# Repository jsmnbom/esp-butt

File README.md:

# esp-butt

Bluetooth intimate hardware (sex toys, etc) controller powered by [buttplug.io](https://buttplug.io/).

## Status

This project is still in fairly early development, it has some quirks and rough edges but is generally functional. Feel free to contact me if you are interested in building your own or contributing to the project.

## Documentation

<div align="center">
  <table>
    <tr>
      <td><h3 align="center"><a href="https://jsmnbom.github.io/esp-butt/">🏠<br/>Home</a></h3></td>
      <td><h3 align="center"><a href="https://jsmnbom.github.io/esp-butt/hardware">🛠️<br/>Hardware</a></h3></td>
      <td><h3 align="center"><a href="https://jsmnbom.github.io/esp-butt/hardware">📋<br/>BOM</a></h3></td>
      <td><h3 align="center"><a href="https://jsmnbom.github.io/esp-butt/hardware">📐<br/>Schematic</a></h3></td>
      <td><h3 align="center"><a href="https://jsmnbom.github.io/esp-butt/hardware">🟩<br/>PCB</a></h3></td>
      <td><h3 align="center"><a href="https://jsmnbom.github.io/esp-butt/hardware">🧊<br/>3D Models</a></h3></td>
      <td><h3 align="center"><a href="https://jsmnbom.github.io/esp-butt/firmware">⚙️<br/>Firmware</a></h3></td>
    </tr>
  </table>
</div>

## Contributing

I welcome contributions with open arms. If you have ideas, suggestions for improvements, or want to help out with development, please don't hesitate to reach out or submit a pull request.

## License

This project uses multiple licenses depending on the component:

| Component | License |
|-----------|---------|
| `src/` — firmware source code | [MIT](https://opensource.org/licenses/MIT) |
| `docs/` — documentation | [MIT](https://opensource.org/licenses/MIT) |
| `cad/` — CAD files | [MIT](https://opensource.org/licenses/MIT) |
| `img/` — images | [CC BY-SA 4.0](https://creativecommons.org/licenses/by-sa/4.0/) |
| `pcb/` — PCB design | [CC BY-SA 4.0](https://creativecommons.org/licenses/by-sa/4.0/) |
| `pcb/kicad-config/10.0/colors/witchhazel.json` | [Apache-2.0](https://www.apache.org/licenses/LICENSE-2.0) — © [Thea Flowers](https://github.com/theacodes/witchhazel) |
| `pcb/esp-butt/3D/` — 3D models | Mixed — see [ATTRIBUTION.md](pcb/esp-butt/3D/ATTRIBUTION.md) |

## Thanks

Thanks to @qdot and the rest of the Buttplug.io contributors doing all the hard work of reverse engineering and protocol design, and also for being generally awesome.

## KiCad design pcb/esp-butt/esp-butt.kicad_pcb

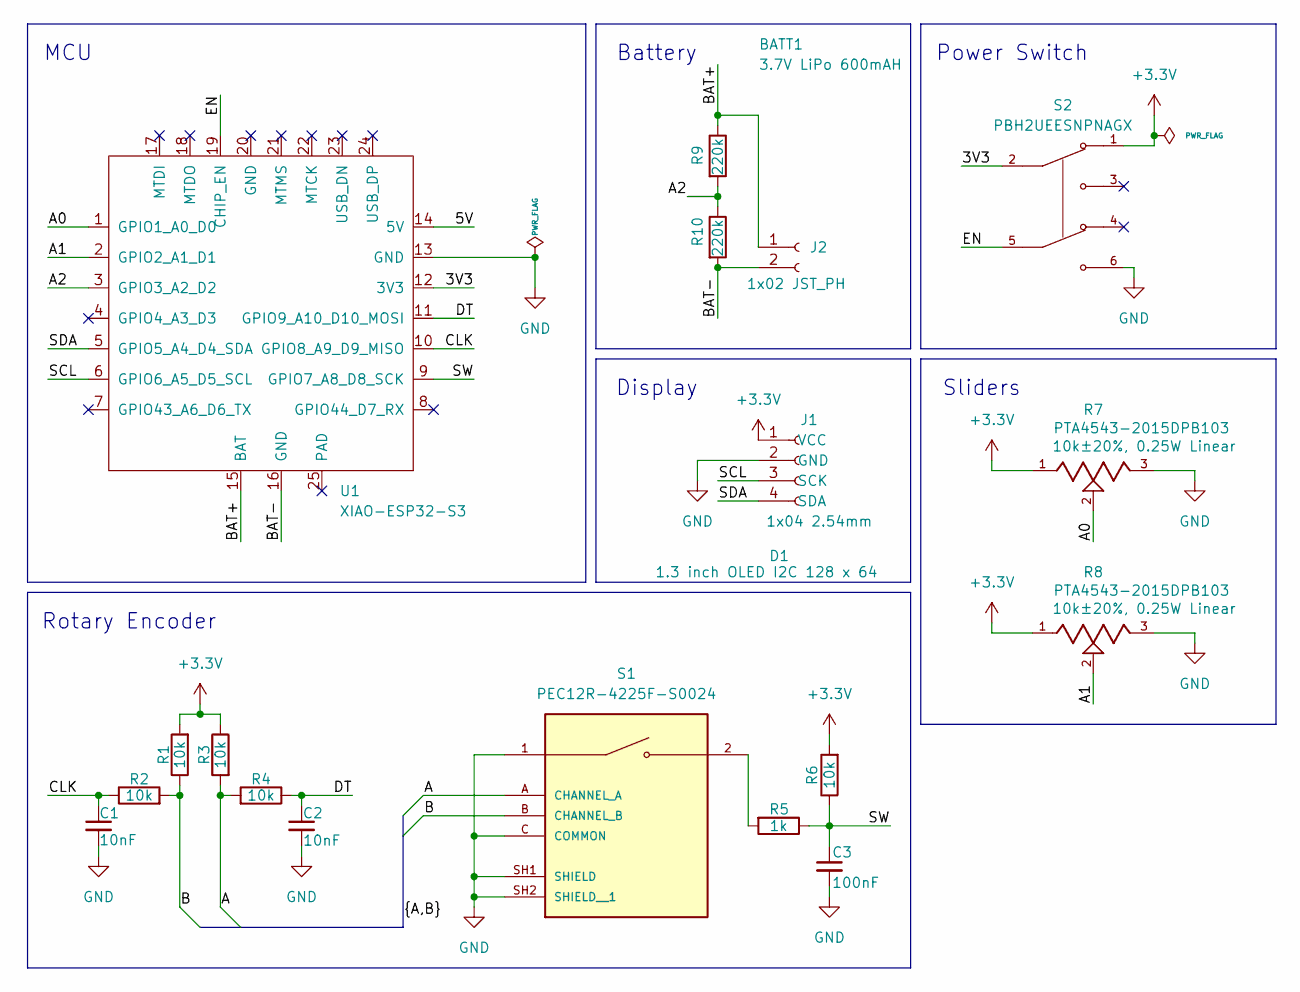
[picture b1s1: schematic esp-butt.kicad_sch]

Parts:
BATT1: 3.7V LiPo 600mAH
C1, C2: 10nF; C_Disc_D5.0mm_W2.5mm_P2.50mm
C3: 100nF; C_Disc_D5.0mm_W2.5mm_P2.50mm
D1: 1.3 inch OLED I2C 128 x 64
J1: 1x04 2.54mm; OLED_128x64_1.3in_I2C_Socket_Vertical
J2: 1x02 JST_PH; JST_PH_B2B-PH-K_1x02_P2.00mm_Vertical
R1, R2, R3, R4, R6: 10k; R_Axial_DIN0207_L6.3mm_D2.5mm_P10.16mm_Horizontal
R5: 1k; R_Axial_DIN0207_L6.3mm_D2.5mm_P10.16mm_Horizontal
R7, R8: PTA4543-2015DPB103; TRIM_PTA4543-2015DPB103; PARTREV 04/21
R9, R10: 220k; R_Axial_DIN0207_L6.3mm_D2.5mm_P10.16mm_Horizontal
S1: PEC12R-4225F-S0024; XDCR_PEC12R-4225F-S0024; PARTREV 07/21
S2: PBH2UEESNPNAGX; SW_PBH2UEESNPNAGX; PARTREV E
U1: XIAO-ESP32-S3; XIAO-ESP32-S3-DIP+

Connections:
+3.3V: J1.1 (VCC), R1.2, R3.1, R6.2, R7.1, R8.1, S2.1
/3V3: S2.2, U1.12 (3V3)
/5V: U1.14 (5V)
/A: R3.2, R4.2, S1.A (CHANNEL_A)
/A0: R7.2, U1.1 (GPIO1_A0_D0)
/A1: R8.2, U1.2 (GPIO2_A1_D1)
/A2: R9.2, R10.1, U1.3 (GPIO3_A2_D2)
/B: R1.1, R2.2, S1.B (CHANNEL_B)
/BAT+: J2.1, R9.1, U1.15 (BAT)
/BAT-: J2.2, R10.2, U1.16 (GND)
/CLK: C1.1, R2.1, U1.10 (GPIO8_A9_D9_MISO)
/DT: C2.1, R4.1, U1.11 (GPIO9_A10_D10_MOSI)
/EN: S2.5, U1.19 (CHIP_EN)
/SCL: J1.3 (SCK), U1.6 (GPIO6_A5_D5_SCL)
/SDA: J1.4 (SDA), U1.5 (GPIO5_A4_D4_SDA)
/SW: C3.1, R5.1, R6.1, U1.9 (GPIO7_A8_D8_SCK)
GND: C1.2, C2.2, C3.2, J1.2 (GND), R7.3, R8.3, S1.1, S1.C (COMMON), S1.SH1 (SHIELD), S1.SH2 (SHIELD__1), S2.6, U1.13 (GND)
unnamed: R5.2, S1.2

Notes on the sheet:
Display
Power Switch
Rotary Encoder
Sliders
MCU
Battery

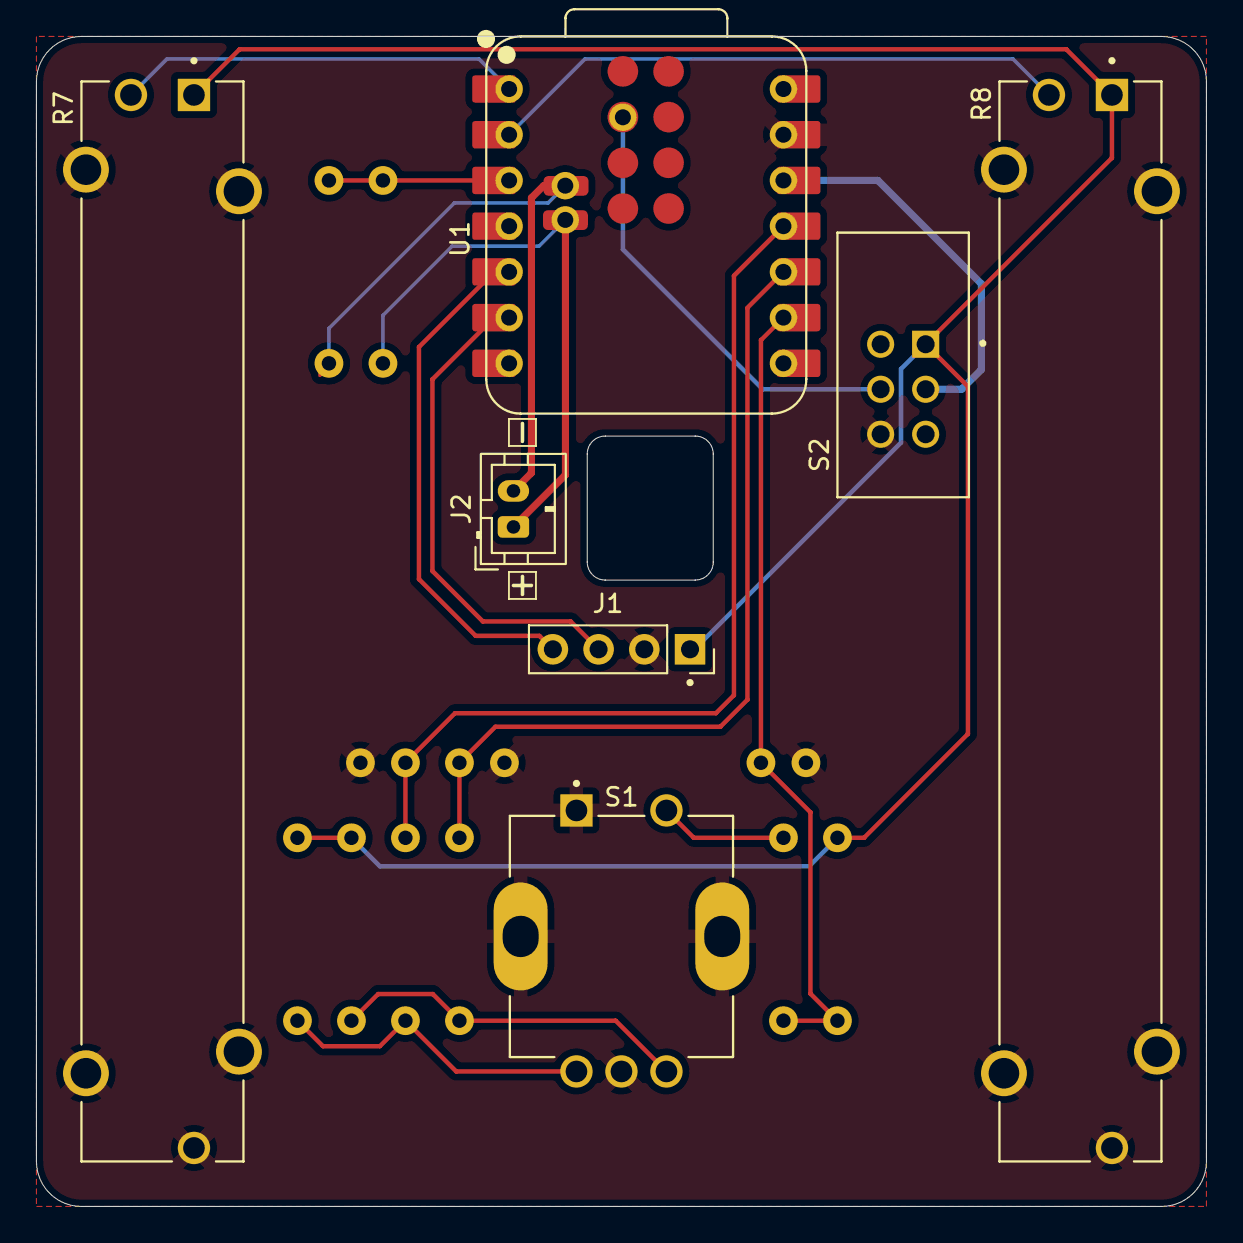
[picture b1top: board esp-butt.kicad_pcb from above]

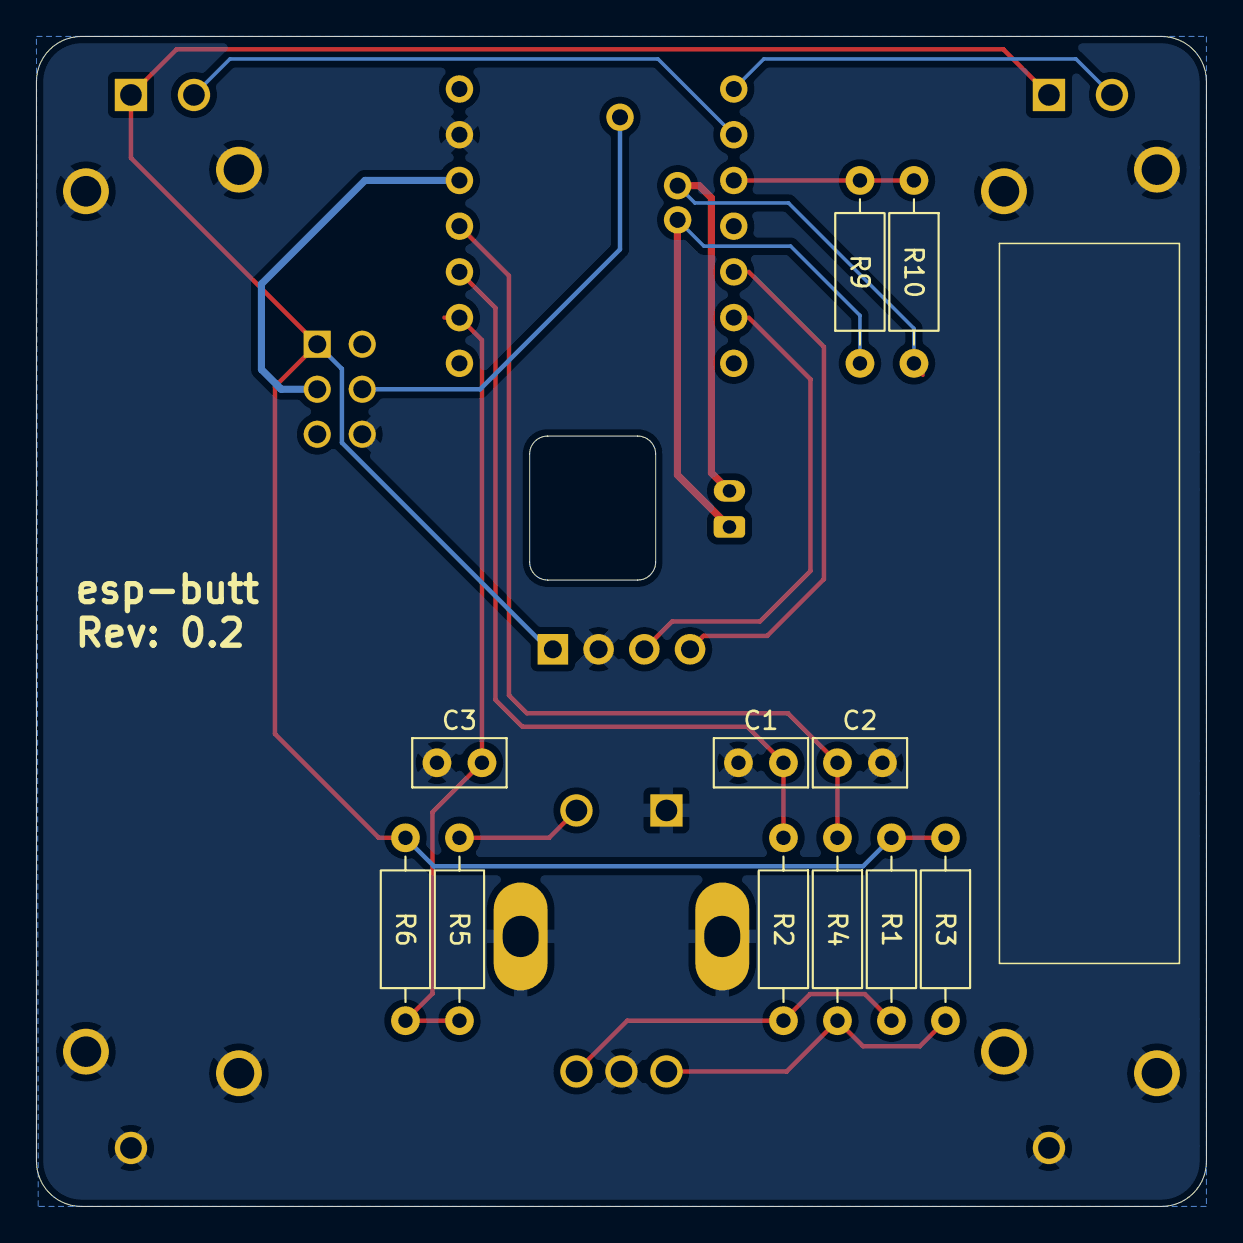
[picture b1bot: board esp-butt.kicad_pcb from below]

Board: 2 copper layers, 65.0 x 65.0 mm, 18 parts (11 on the bottom side), 17 nets.

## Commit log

2026-02-16 Initial
2026-02-17 Almost working
2026-02-18 working
    well - at least it's connecting to a device
2026-02-26 work
2026-02-28 more work
2026-03-07 Worky work
2026-03-07 Add PCB
    ... i wonder what the license of those footprint files is...?
2026-03-13 More stuffs
2026-03-15 oh wow stuff!
2026-03-21 More worky
2026-03-29 Stuffs
2026-03-30 things
2026-04-02 cad updates
2026-04-05 meow
2026-04-06 meowmeow
2026-04-08 big meow
2026-04-08 smol fixes
2026-04-11 Robustness improvements
2026-04-13 workies
2026-04-23 More work + docs
2026-04-23 workflow
2026-04-23 Fix deps
2026-04-23 Fix CI workflows: replace broken xtensa-toolchain action with espup, fix build syntax error, fix docs container permissions
    Agent-Logs-Url: https://github.com/jsmnbom/esp-butt/sessions/dd848015-c231-475d-9a6b-b27d4dc768ed
2026-04-23 Pin espup to v0.17.1 and cache ldproxy binary
    Agent-Logs-Url: https://github.com/jsmnbom/esp-butt/sessions/dd848015-c231-475d-9a6b-b27d4dc768ed
2026-04-23 Add workflow_dispatch to firmware and docs workflows
    Agent-Logs-Url: https://github.com/jsmnbom/esp-butt/sessions/8c52e418-970e-4b85-befa-792ccc4bc05c
2026-04-23 Add unzip to system dependencies in docs workflow
2026-04-23 CI fixes
2026-04-23 Fix dead link
2026-04-26 Add Pillow dependency and implement session recording feature
    - Added "pillow" to dependencies in pyproject.toml and uv.lock.
    - Enhanced HardwareMock to support session recording, including:
    - New spawn_recorder_task function to handle event and frame recording.
    - Logic to create a temporary directory for storing frames.
    - Recording navigation and slider events to a specified NDJSON file.
    - Saving frames as PNG images during the session.
2026-04-27 hero improvements
2026-04-27 feat: enhance recording functionality and improve documentation
    - Added `useRecording` composable to load and process session recordings with GIF frames.
    - Updated CSS for better layout and responsiveness of the hero image area.
    - Integrated new components in the theme index and improved model imports in documentation.
    - Refactored model download components to use dynamic URLs.
    - Updated TypeScript configuration to include path mappings for easier imports.
    - Enhanced NDJSON module declaration for better type safety.
2026-04-27 feat: add Vite image optimizer and SVGO for enhanced image processing
2026-04-28 Documentation updates
2026-04-28 better icons
2026-04-28 Fix spelling
2026-04-29 Update deps and add licensing
2026-04-29 Use h3 for readme links
2026-04-29 Fix readme link nesting
2026-04-29 Fix workflows
